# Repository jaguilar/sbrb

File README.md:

# SBRB -- Another Arduino-based Self-Balancing Robot

## Overview

Well, is it really Arduino based? A little bit, but it's a funky
hybrid of ESP-IDF and Arduino code. This bot can be controlled
using a BLE gamepad like the Steam Controller (BLE firmware).

## Features

- Remote controllable
- Self-balancing
- Telemetry and bluetooth-based tuning
- Battery monitoring (assumes 2S LiPo, see schematics for voltage divider
  requirements)

## Schematics

There is a sort-of-working KiCad schematic in the `kicad` directory.
This is not actually what I used: I soldered together a protoboard.
Also, the pin configuration on the proto board and in the code is
significantly altered from what is shown in the schematic.

## Building

The bot uses 3D printed parts from this [OnShape document](https://cad.onshape.com/documents/8def695b0fbd504a5c261cca/w/9027d04ea9ab3dbc2eeb5165/e/62757f7892dd92c4c3207e76?renderMode=0&uiState=6980eee3efbda49a56e499ec).

## BOM

In addition to the 3D printed parts, you need:

* 2x 693ZZ bearings
* 2x 500 RPM N20 motors with gearboxes (I used [these](https://www.aliexpress.us/item/3256807135186419.html?spm=a2g0o.order_list.order_list_main.5.16f118023HkDq9&gatewayAdapt=glo2usa))
* 2x TT motor wheels
* 1x 50x70mm perfboard
* 1x MPU-6050 breakout board
* 1x ESP32-S3 Zero Dev board
* 1x Mini360 buck converter
* 1x 20k resistor (buy a 0508 assortment of SMD parts, should have the caps and diode too)
* 1x 10k resistor
* 2x 100nF capacitor SMD 
* 1x 470uF capacitor throughhole (buy an assortment)
* 1x 100uF capacitor throughhole
* 1x 1N5819 Schottky diode
* 1x 3A fuse (you can use less, 2A would be fine)
* 1x throughhole switch capable of supporting same amperage as your
  fuse, or a lesser amperage and a MOSFET capable of supporting that current
* 1x TB6612FNG motor driver breakout board
* 1x 2S LiPo battery
* 3x JST-XH 2 pin through hole header
* 2x JST-XH 4 pin through hole header
* JST-XH female connectors for wires
* Various M2 and M3 hex head screws and nuts
* Various 24 AWG hookup wire
* XT30 connectors for battery

## Media

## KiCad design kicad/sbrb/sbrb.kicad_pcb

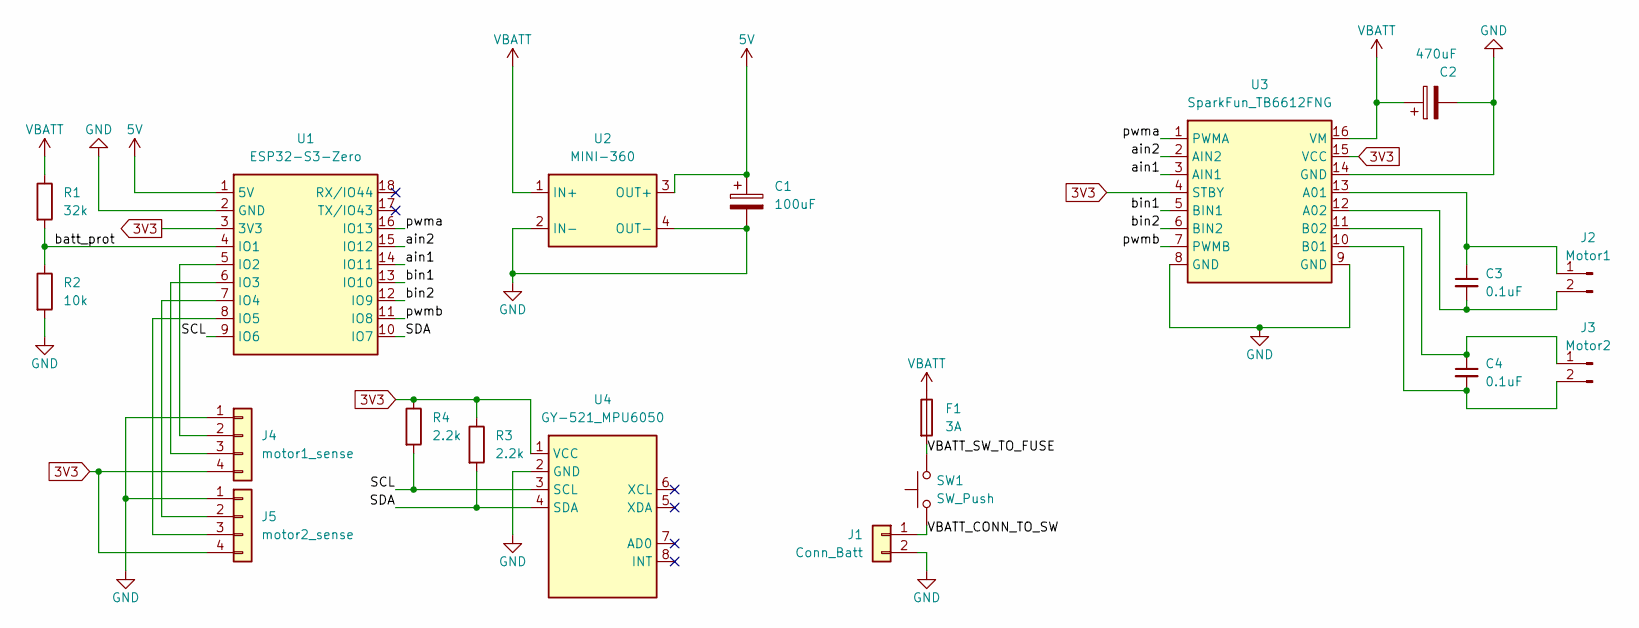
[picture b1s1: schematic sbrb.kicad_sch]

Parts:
C1: 100uF; CP_Radial_D6.3mm_P2.50mm
C2: 470uF; CP_Radial_D8.0mm_P3.80mm
C3, C4: 0.1uF; C_0805_2012Metric
F1: 3A; Fuse_Schurter_UMT250
J1: Conn_Batt; JST_XH_B2B-XH-AM_1x02_P2.50mm_Vertical
J2: Motor1; JST_XH_B2B-XH-AM_1x02_P2.50mm_Vertical
J3: Motor2; JST_XH_B2B-XH-AM_1x02_P2.50mm_Vertical
J4: motor1_sense; JST_XH_B4B-XH-AM_1x04_P2.50mm_Vertical
J5: motor2_sense; JST_XH_B4B-XH-AM_1x04_P2.50mm_Vertical
R1: 32k; R_0805_2012Metric
R2: 10k; R_0805_2012Metric
R3, R4: 2.2k; R_0805_2012Metric
SW1: SW_Push; SW_SPST_FSMSM
U1: ESP32-S3-Zero; ESP32-S3-Zero_Breakout
U2: MINI-360; mini360
U3: SparkFun_TB6612FNG; TB6612FNG_Breakout
U4: GY-521_MPU6050; GY-521

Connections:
3V3: J4.4, J5.4, R3.1, R4.1, U1.3 (3V3), U3.4 (STBY), U3.15 (VCC), U4.1 (VCC)
5V: C1.1, U1.1 (5V), U2.3 (OUT+)
/SCL: R4.2, U1.9 (IO6), U4.3 (SCL)
/SDA: R3.2, U1.10 (IO7), U4.4 (SDA)
/VBATT_CONN_TO_SW: J1.1, SW1.1
/VBATT_SW_TO_FUSE: F1.2, SW1.2
/ain1: U1.14 (IO11), U3.3 (AIN1)
/ain2: U1.15 (IO12), U3.2 (AIN2)
/batt_prot: R1.2, R2.1, U1.4 (IO1)
/bin1: U1.13 (IO10), U3.5 (BIN1)
/bin2: U1.12 (IO9), U3.6 (BIN2)
/pwma: U1.16 (IO13), U3.1 (PWMA)
/pwmb: U1.11 (IO8), U3.7 (PWMB)
GND: C1.2, C2.2, J1.2, J4.1, J5.1, R2.2, U1.2 (GND), U2.2 (IN-), U2.4 (OUT-), U3.8 (GND), U3.9 (GND), U3.14 (GND), U4.2 (GND)
unnamed: C3.1, J2.1, U3.13 (A01)
unnamed: C3.2, J2.2, U3.12 (A02)
unnamed: C4.1, J3.1, U3.11 (B02)
unnamed: C4.2, J3.2, U3.10 (B01)
unnamed: J4.2, U1.5 (IO2)
unnamed: J4.3, U1.6 (IO3)
unnamed: J5.2, U1.7 (IO4)
unnamed: J5.3, U1.8 (IO5)
VBATT: C2.1, F1.1, R1.1, U2.1 (IN+), U3.16 (VM)

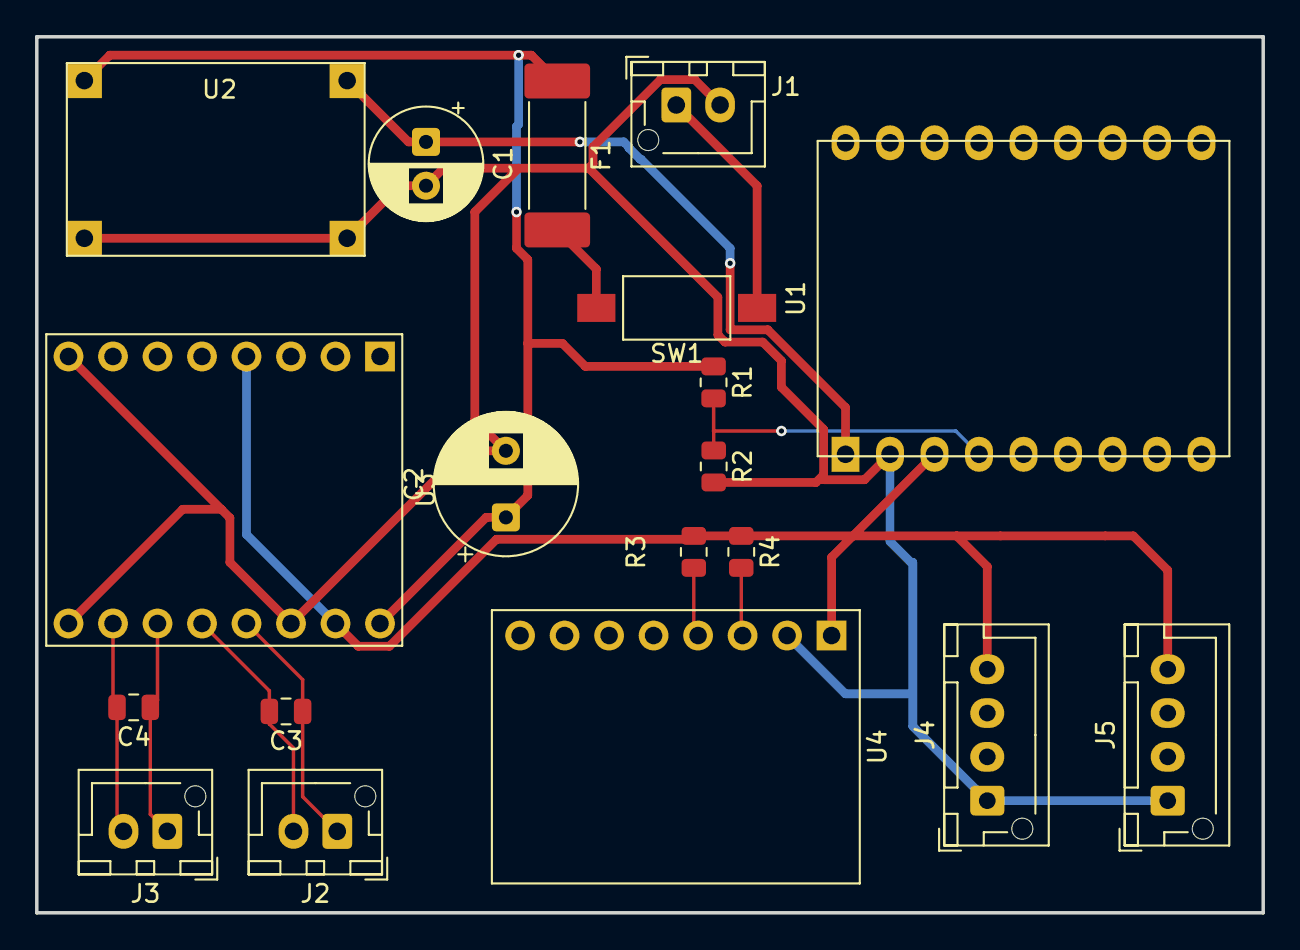
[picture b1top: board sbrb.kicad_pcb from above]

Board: 4 copper layers, 70.0 x 50.0 mm, 19 parts (0 on the bottom side), 23 nets.

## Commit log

2026-01-26 Various updates, kicad schematic
2026-01-27 Initial schematic
2026-01-27 Finishe design
2026-01-29 Guard speed under the spinlock as well.
2026-01-29 Update gitignore.
2026-01-29 Add more of the utility code.
2026-01-29 Separate deep sleep concerns into methods.
2026-01-29 Add diode to schematic.
2026-01-30 Basically working
2026-01-30 Final tweaks. It works.
2026-01-30 Add needed diode.
2026-01-31 Reduce frequency of steering control.
2026-01-31 Add some consts.
2026-01-31 Update constants a bit more.
2026-02-02 Complete rework for ESP-IDF.
2026-02-02 Fix links.
2026-02-02 Fix links again!
2026-02-03 Rework media section
2026-02-04 Fix link to youtube video.
2026-02-04 Revise BOM with additional components and clarifications
    Updated parts list with additional details and corrections.
